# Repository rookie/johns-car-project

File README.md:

Overview
========

The goal of this project it to build a display for a car's instrument panel.

Display will include
- Engine coolant temp
- External temp
- Internal temp
- Speed (from GPS)
- Time (from GPS)
- Date (from GPS)
- Button input to toggle display between Metric to Imperial
- Button input to toggle time offset for Daylight Saving

Parts List
==========

- 1x Arduino Pro Mini 328 - https://www.sparkfun.com/products/11113
- 1x Adafruit 2.2" LCD - http://www.adafruit.com/products/1480
- 1x Adafruit Ultimate GPS - http://www.adafruit.com/products/746
- 3x ACDelco / GM Ambient Temperature Sensor (10K @ 25°C) - http://www.newgmparts.com/oe-gm/15936931

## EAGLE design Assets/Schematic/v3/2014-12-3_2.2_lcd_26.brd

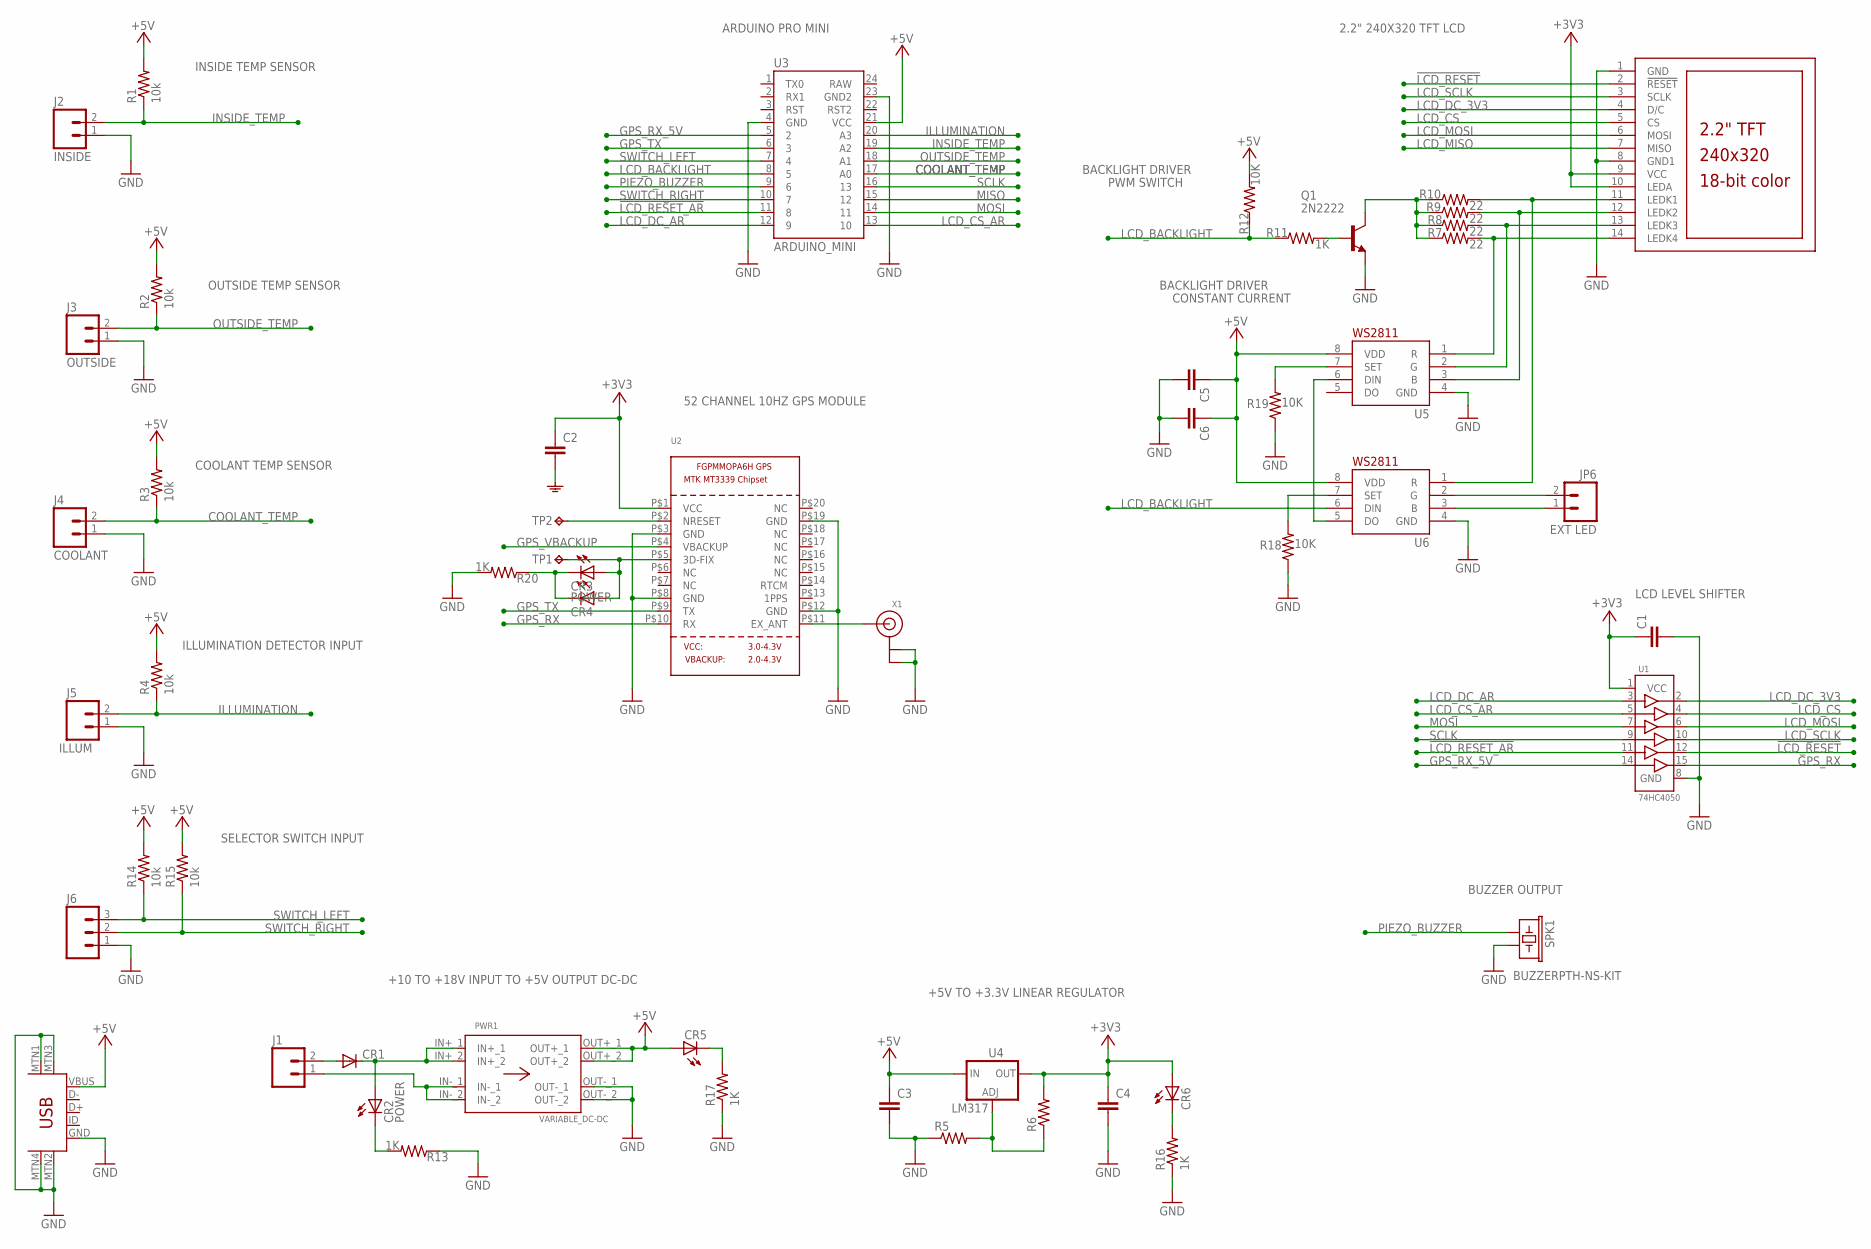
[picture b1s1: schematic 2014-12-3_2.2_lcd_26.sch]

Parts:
C1, C2, C3, C4, C5, C6: CAP0805; 0805
CR1: DIODESMB; SMB-DIODE
CR2, CR3: POWER; LED3MM
CR4, CR5, CR6: LED0603; LED-0603
J1: M02POLAR; MOLEX-1X2
J2: INSIDE; MOLEX-1X2
J3: OUTSIDE; MOLEX-1X2
J4: COOLANT; MOLEX-1X2
J5: ILLUM; MOLEX-1X2
J6: M03POLAR; MOLEX-1X3
JP6: EXT LED; MOLEX-1X2
PWR1: VARIABLE_DC-DC
Q1: 2N2222; TO92
R1, R2, R3, R4, R14, R15: 10k; 0805
R5, R6: RESISTOR0805-RES; 0805
R7, R8, R9, R10: 22; 0805
R11, R13, R16, R17, R20: 1K; 0805
R12, R18, R19: 10K; 0805
SPK1: BUZZERPTH-NS-KIT; BUZZER-12MM-NS-KIT
TP1, TP2: TPPAD1-13; P1-13
U1: 74HC4050; SO16
U2: GPS_FGPMMOPA6H; FGPMMOPA6H
U3: ARDUINO_MINI
U4: LM317; SOT223
U5, U6: WS2811-SOP8; SO08-SKINNYPADS
U$2: 2.2_LCD
USB: USB-MINIB-5PIN; USB-MINIB
X1: ANTENNA_U.FL; U.FL

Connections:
!LCD_RESET: U1.12, U$2.2 (!RESET)
!LCD_RESET_AR: U1.11, U3.11 (8)
+3V3: C1.1, C2.1, C4.1, CR6.A, R6.2, U1.1 (VCC), U2.P$1 (VCC), U4.2 (OUT), U$2.9 (VCC), U$2.10 (LEDA)
+5V: C3.1, C5.1, C6.1, CR5.A, PWR1.OUT+_1, PWR1.OUT+_2, R1.2, R2.2, R3.2, R4.2, R12.2, R14.2, R15.2, U3.21 (VCC), U4.3 (IN), U5.8 (VDD), U6.8 (VDD), USB.VBUS
COOLANT_TEMP: J4.2, R3.1, U3.17 (A0)
GND: C1.2, C3.2, C4.2, C5.2, C6.2, J2.1, J3.1, J4.1, J5.1, J6.1, PWR1.OUT-_1, PWR1.OUT-_2, Q1.1 (E), R5.1, R13.1, R16.1, R17.1, R18.1, R19.1, R20.2, SPK1.- (2), U1.8 (GND), U2.P$3 (GND), U2.P$8 (GND), U2.P$12 (GND), U2.P$19 (GND), U3.4 (GND), U3.23 (GND2), U5.4 (GND), U6.4 (GND), U$2.1 (GND), U$2.8 (GND1), USB.GND, USB.MTN1 (MTN2), USB.MTN2 (MTN3), USB.MTN3 (MTN1), USB.MTN4, X1.1 (GND), X1.2 (GND)
GPS_RX: U1.15, U2.P$10 (RX)
GPS_RX_5V: U1.14, U3.5 (2)
GPS_TX: U2.P$9 (TX), U3.6 (3)
GPS_VBACKUP: U2.P$4 (VBACKUP)
ILLUMINATION: J5.2, R4.1, U3.20 (A3)
INSIDE_TEMP: J2.2, R1.1, U3.19 (A2)
LCD_BACKLIGHT: R11.1, R12.1, U3.8 (5), U6.6 (DIN)
LCD_CS: U1.4, U$2.5 (CS)
LCD_CS_AR: U1.5, U3.13 (10)
LCD_DC_3V3: U1.2, U$2.4 (D/C)
LCD_DC_AR: U1.3, U3.12 (9)
LCD_MISO: U$2.7 (MISO)
LCD_MOSI: U1.6, U$2.6 (MOSI)
LCD_SCLK: U1.10, U$2.3 (SCLK)
MISO: U3.15 (12)
MOSI: U1.7, U3.14 (11)
unnamed: TP2.TP, U2.P$2 (NRESET)
unnamed: U2.P$11 (EX_ANT), X1.3 (SIGNAL)
unnamed: R7.2, U5.1 (R), U$2.14 (LEDK4)
unnamed: R8.2, U5.2 (G), U$2.13 (LEDK3)
unnamed: R9.2, U5.3 (B), U$2.12 (LEDK2)
unnamed: R5.2, R6.1, U4.1 (ADJ)
unnamed: R10.2, U6.1 (R), U$2.11 (LEDK1)
unnamed: Q1.3 (C), R7.1, R8.1, R9.1, R10.1
unnamed: Q1.2 (B), R11.2
unnamed: CR1.A, J1.2
unnamed: CR1.C, CR2.A, PWR1.IN+_1, PWR1.IN+_2
unnamed: J1.1, PWR1.IN-_1, PWR1.IN-_2
unnamed: JP6.2, U6.2 (G)
unnamed: CR3.K (C), CR4.C, R20.1
unnamed: CR2.K (C), R13.2
unnamed: CR3.A, CR4.A, TP1.TP, U2.P$5 (3D-FIX)
unnamed: CR6.C, R16.2
unnamed: CR5.C, R17.2
unnamed: U5.6 (DIN), U6.5 (DO)
unnamed: R18.2, U6.7 (SET)
unnamed: JP6.1, U6.3 (B)
unnamed: R19.2, U5.7 (SET)
OUTSIDE_TEMP: J3.2, R2.1, U3.18 (A1)
P$1: C2.2
PIEZO_BUZZER: SPK1.+ (1), U3.9 (6)
SCLK: U1.9, U3.16 (13)
SWITCH_LEFT: J6.3, R14.1, U3.7 (4)
SWITCH_RIGHT: J6.2, R15.1, U3.10 (7)

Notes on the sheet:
ARDUINO PRO MINI
2.2" 240X320 TFT LCD
BACKLIGHT DRIVER
CONSTANT CURRENT
PWM SWITCH
LCD LEVEL SHIFTER
BUZZER OUTPUT
+5V TO +3.3V LINEAR REGULATOR
+10 TO +18V INPUT TO +5V OUTPUT DC-DC
SELECTOR SWITCH INPUT
ILLUMINATION DETECTOR INPUT
COOLANT TEMP SENSOR
OUTSIDE TEMP SENSOR
INSIDE TEMP SENSOR
52 CHANNEL 10HZ GPS MODULE

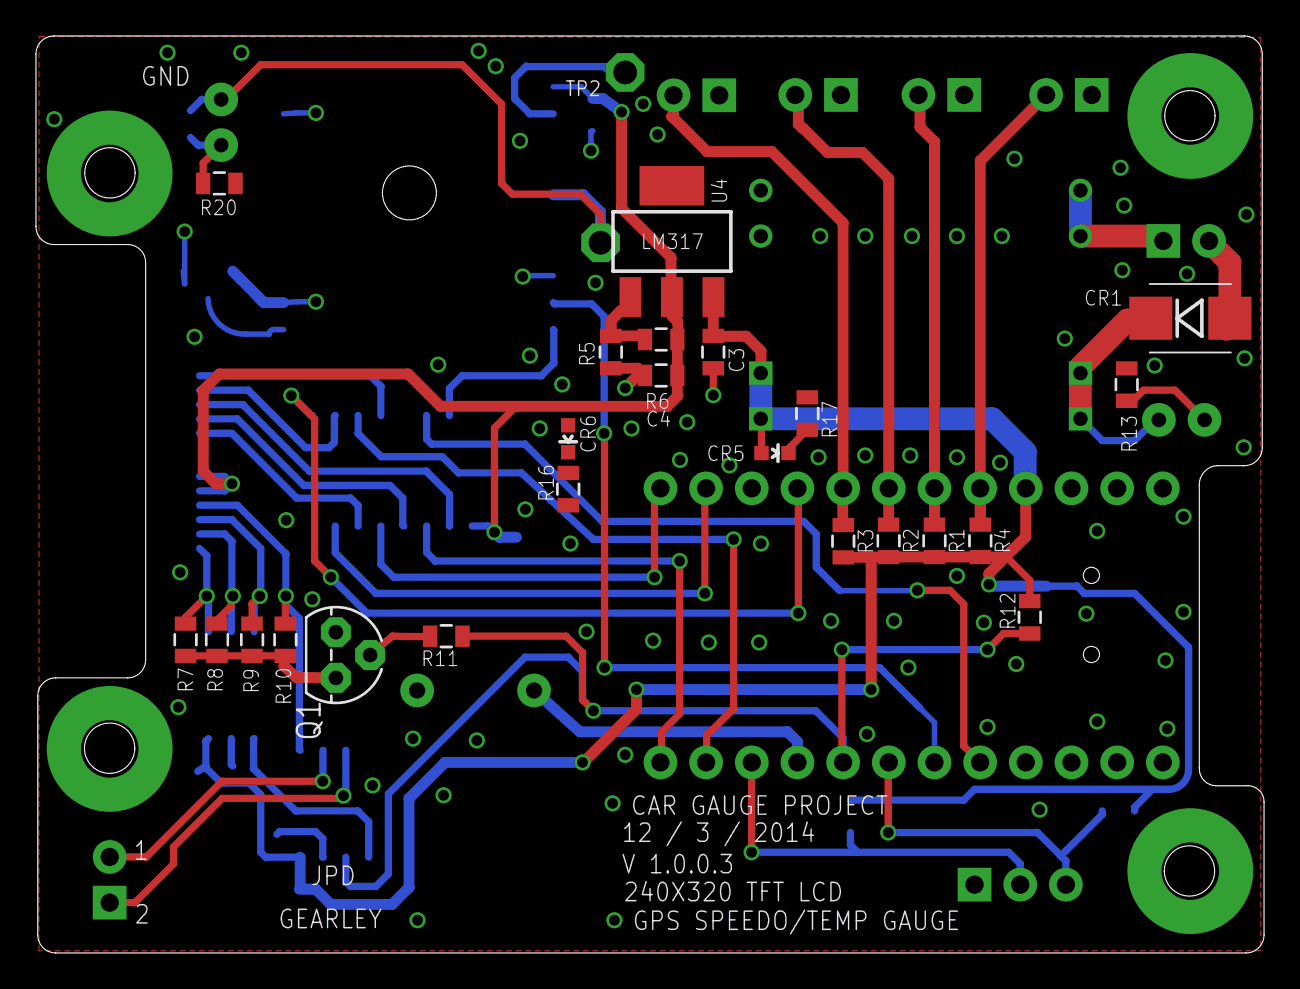
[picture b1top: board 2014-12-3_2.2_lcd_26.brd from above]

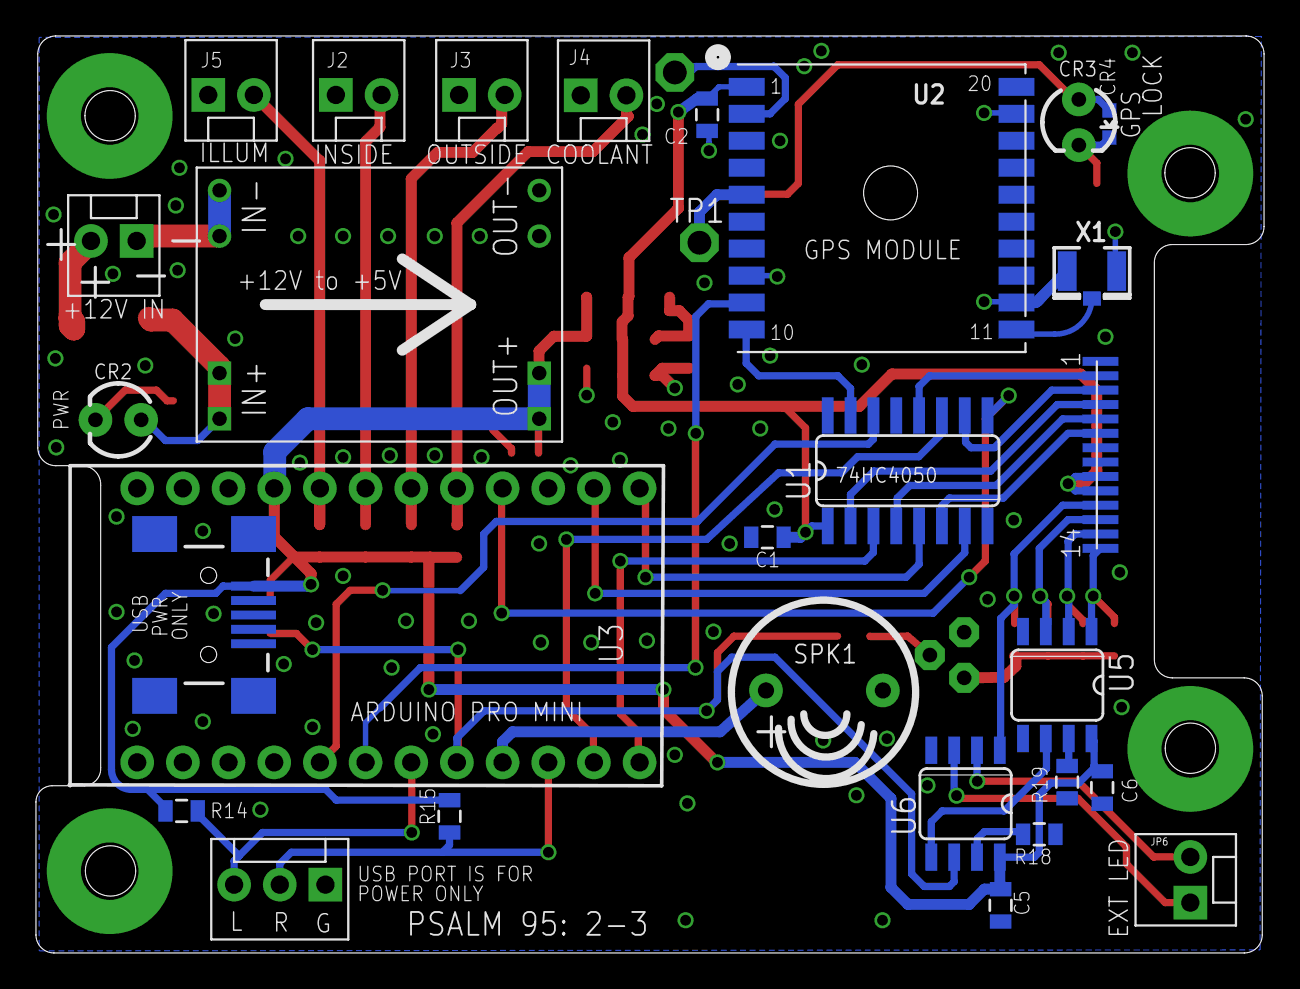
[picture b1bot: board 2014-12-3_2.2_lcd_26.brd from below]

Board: 2 copper layers, 68.3 x 51.0 mm, 53 parts (29 on the bottom side), 46 nets.

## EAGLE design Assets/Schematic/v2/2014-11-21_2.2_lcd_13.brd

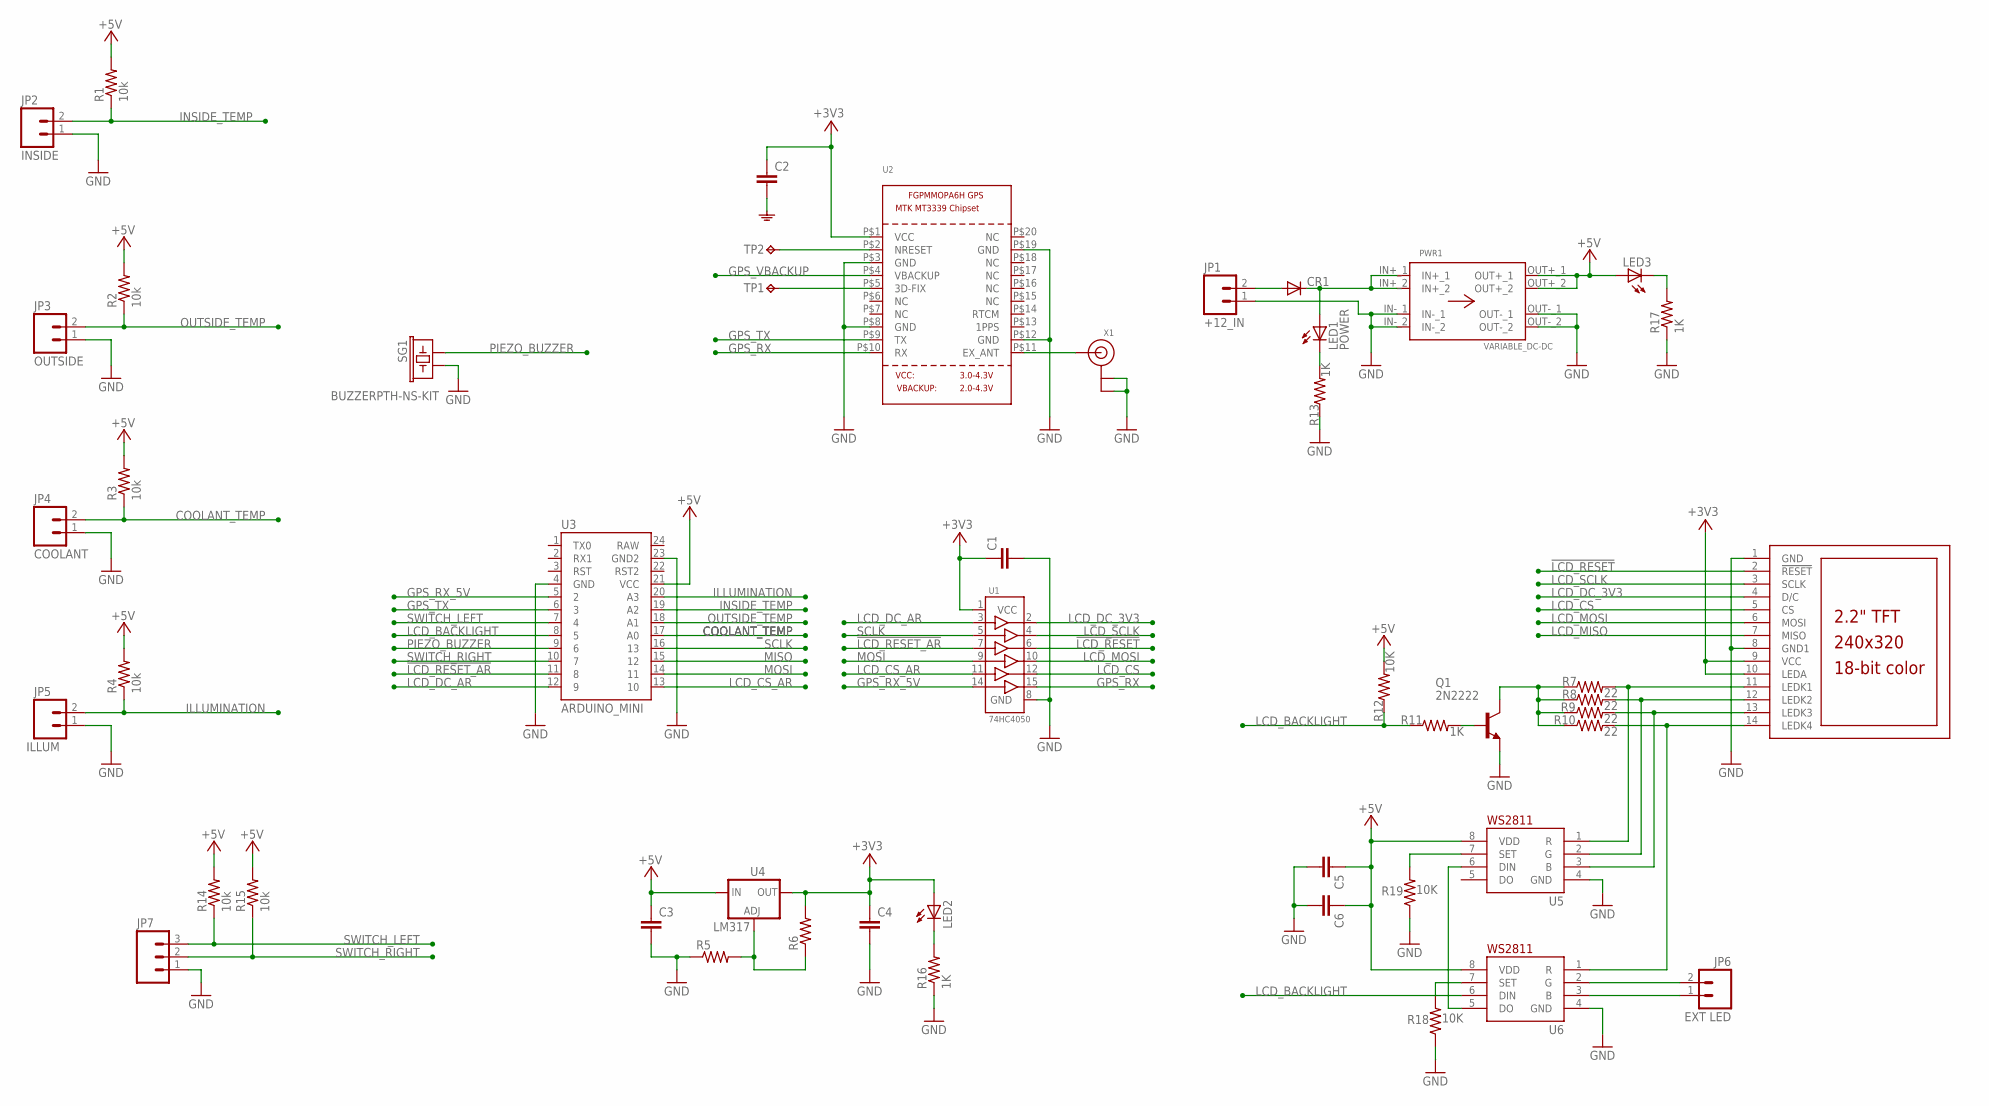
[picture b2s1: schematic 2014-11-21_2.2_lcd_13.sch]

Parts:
C1, C2, C3, C4: CAP0805; 0805
C5, C6: CAP0603-CAP; 0603-CAP
CR1: DIODESMA-ALT; SMA-DIODE_ALT
JP1: +12_IN; JST-2-PTH-VERT
JP2: INSIDE; JST-2-PTH-VERT
JP3: OUTSIDE; JST-2-PTH-VERT
JP4: COOLANT; JST-2-PTH-VERT
JP5: ILLUM; JST-2-PTH-VERT
JP6: EXT LED; JST-2-PTH-VERT
JP7: M03POLAR; MOLEX-1X3
LED1: POWER; LED3MM
LED2, LED3: LED0603; LED-0603
PWR1: VARIABLE_DC-DC
Q1: 2N2222; TO92
R1, R2, R3, R4, R14, R15: 10k; 0805
R5, R6: RESISTOR0805-RES; 0805
R7, R8, R9, R10: 22; 0805
R11, R13, R16, R17: 1K; 0805
R12, R18, R19: 10K; 0805
SG1: BUZZERPTH-NS-KIT; BUZZER-12MM-NS-KIT
TP1, TP2: TPPAD1-13; P1-13
U1: 74HC4050; SO16
U2: GPS_FGPMMOPA6H; FGPMMOPA6H
U3: ARDUINO_MINI
U4: LM317; SOT223
U5, U6: WS2811-SOP8; SO08-SKINNYPADS
U$1: 2.2_LCD
X1: ANTENNA_U.FL; U.FL

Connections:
!LCD_RESET: U1.6, U$1.2 (!RESET)
!LCD_RESET_AR: U1.7, U3.11 (8)
+3V3: C1.1, C2.1, C4.1, LED2.A, R6.2, U1.1 (VCC), U2.P$1 (VCC), U4.2 (OUT), U$1.9 (VCC), U$1.10 (LEDA)
+5V: C3.1, C5.1, C6.1, LED3.A, PWR1.OUT+_1, PWR1.OUT+_2, R1.2, R2.2, R3.2, R4.2, R12.2, R14.2, R15.2, U3.21 (VCC), U4.3 (IN), U5.8 (VDD), U6.8 (VDD)
COOLANT_TEMP: JP4.2, R3.1, U3.17 (A0)
GND: C1.2, C3.2, C4.2, C5.2, C6.2, JP1.1, JP2.1, JP3.1, JP4.1, JP5.1, JP7.1, PWR1.IN-_1, PWR1.IN-_2, PWR1.OUT-_1, PWR1.OUT-_2, Q1.1 (E), R5.1, R13.1, R16.1, R17.1, R18.1, R19.1, SG1.- (2), U1.8 (GND), U2.P$3 (GND), U2.P$8 (GND), U2.P$12 (GND), U2.P$19 (GND), U3.4 (GND), U3.23 (GND2), U5.4 (GND), U6.4 (GND), U$1.1 (GND), U$1.8 (GND1), X1.1 (GND), X1.2 (GND)
GPS_RX: U1.15, U2.P$10 (RX)
GPS_RX_5V: U1.14, U3.5 (2)
GPS_TX: U2.P$9 (TX), U3.6 (3)
GPS_VBACKUP: U2.P$4 (VBACKUP)
ILLUMINATION: JP5.2, R4.1, U3.20 (A3)
INSIDE_TEMP: JP2.2, R1.1, U3.19 (A2)
LCD_BACKLIGHT: R11.1, R12.1, U3.8 (5), U6.6 (DIN)
LCD_CS: U1.12, U$1.5 (CS)
LCD_CS_AR: U1.11, U3.13 (10)
LCD_DC_3V3: U1.2, U$1.4 (D/C)
LCD_DC_AR: U1.3, U3.12 (9)
LCD_MISO: U$1.7 (MISO)
LCD_MOSI: U1.10, U$1.6 (MOSI)
LCD_SCLK: U1.4, U$1.3 (SCLK)
MISO: U3.15 (12)
MOSI: U1.9, U3.14 (11)
unnamed: TP2.TP, U2.P$2 (NRESET)
unnamed: U2.P$11 (EX_ANT), X1.3 (SIGNAL)
unnamed: R7.2, U5.1 (R), U$1.11 (LEDK1)
unnamed: R8.2, U5.2 (G), U$1.12 (LEDK2)
unnamed: R9.2, U5.3 (B), U$1.13 (LEDK3)
unnamed: R5.2, R6.1, U4.1 (ADJ)
unnamed: R10.2, U6.1 (R), U$1.14 (LEDK4)
unnamed: Q1.3 (C), R7.1, R8.1, R9.1, R10.1
unnamed: Q1.2 (B), R11.2
unnamed: CR1.A, JP1.2
unnamed: CR1.C, LED1.A, PWR1.IN+_1, PWR1.IN+_2
unnamed: JP6.2, U6.2 (G)
unnamed: LED1.K (C), R13.2
unnamed: TP1.TP, U2.P$5 (3D-FIX)
unnamed: LED2.C, R16.2
unnamed: LED3.C, R17.2
unnamed: U5.6 (DIN), U6.5 (DO)
unnamed: R18.2, U6.7 (SET)
unnamed: JP6.1, U6.3 (B)
unnamed: R19.2, U5.7 (SET)
OUTSIDE_TEMP: JP3.2, R2.1, U3.18 (A1)
P$1: C2.2
PIEZO_BUZZER: SG1.+ (1), U3.9 (6)
SCLK: U1.5, U3.16 (13)
SWITCH_LEFT: JP7.3, R14.1, U3.7 (4)
SWITCH_RIGHT: JP7.2, R15.1, U3.10 (7)

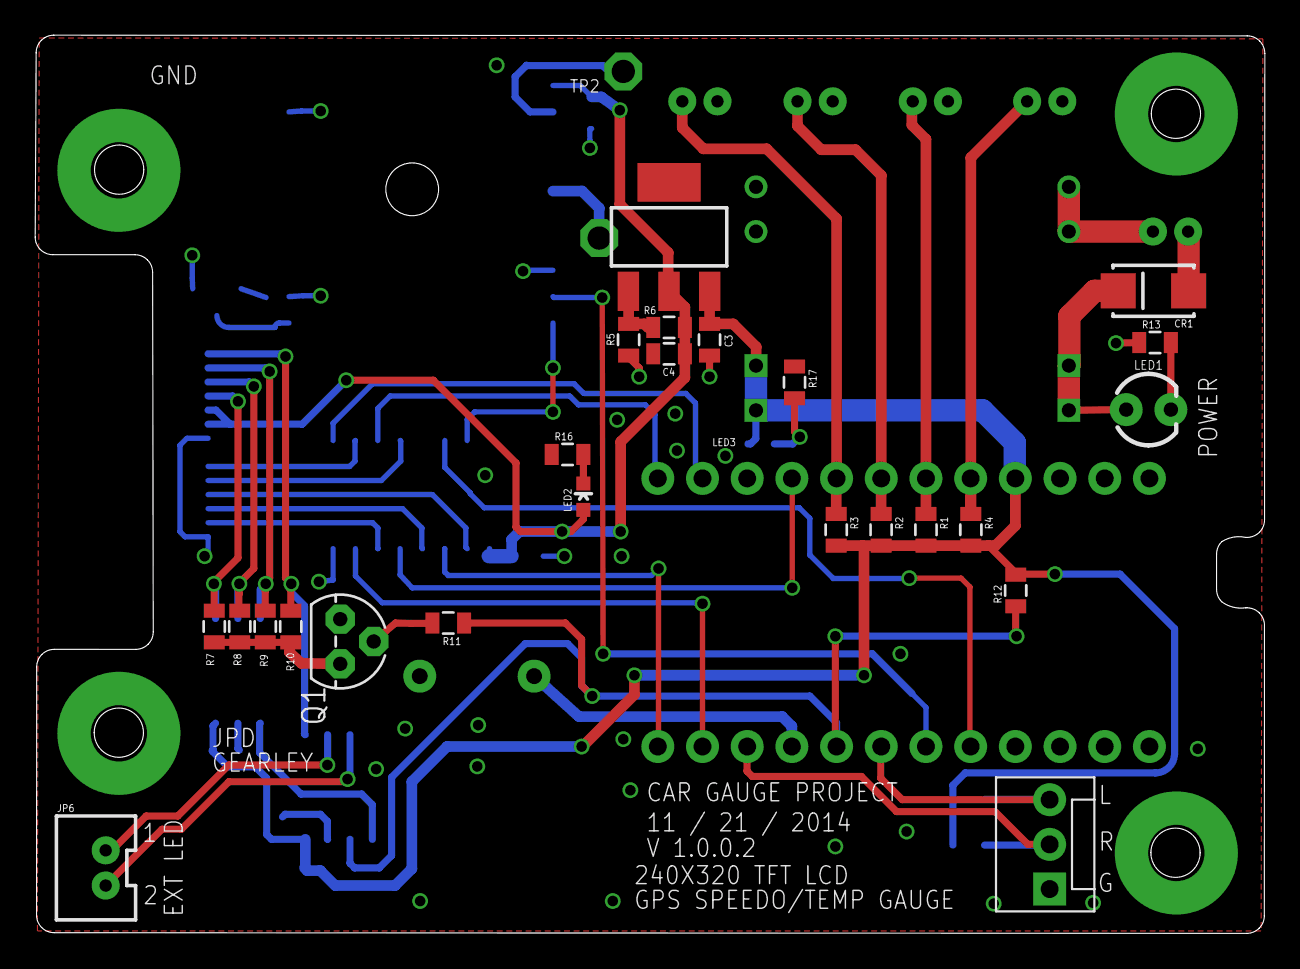
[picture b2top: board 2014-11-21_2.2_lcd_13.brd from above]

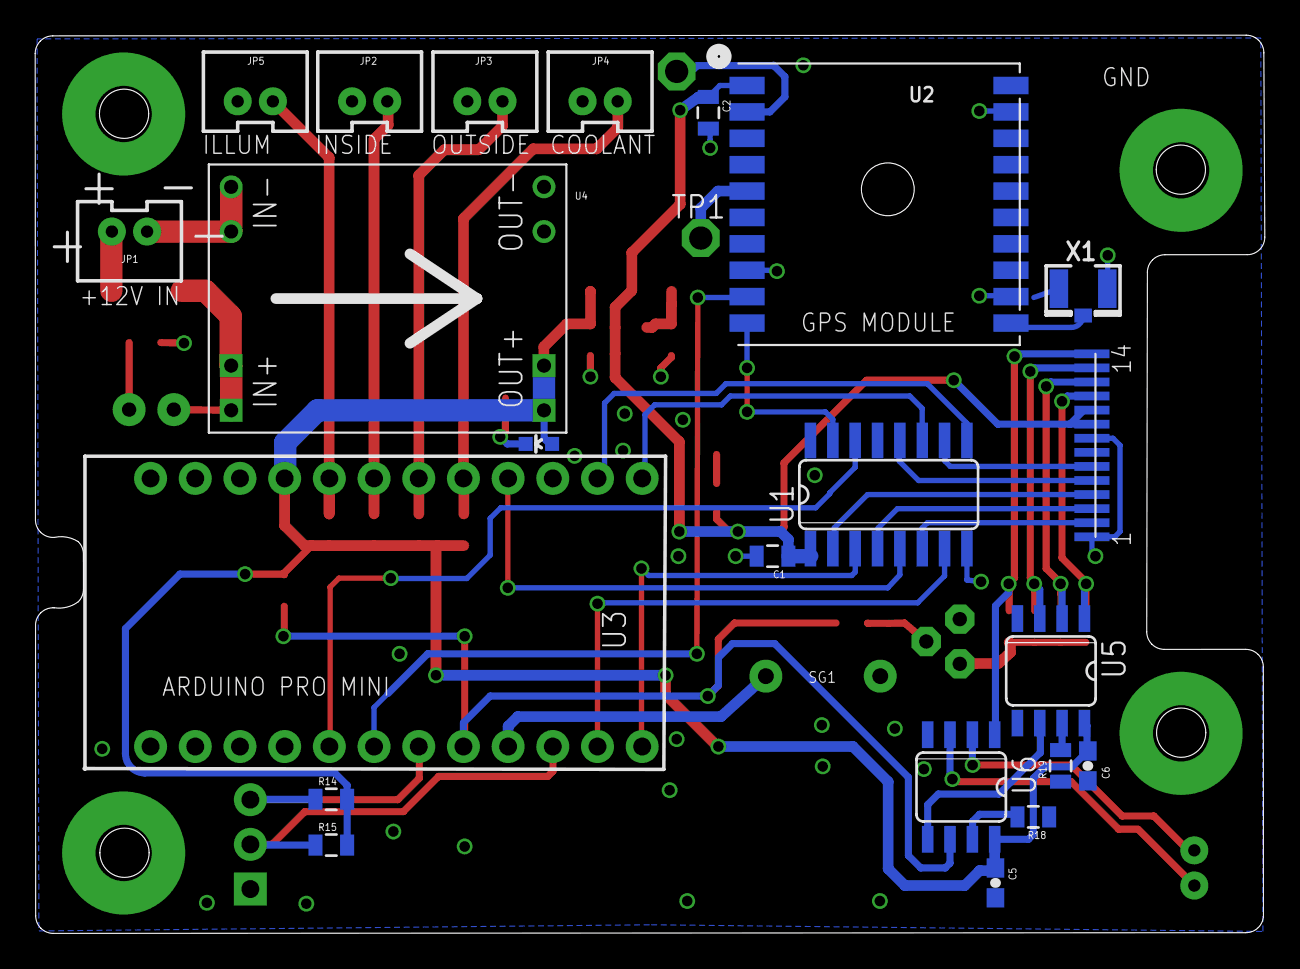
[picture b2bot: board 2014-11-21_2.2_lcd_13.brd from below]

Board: 2 copper layers, 69.9 x 51.0 mm, 49 parts (24 on the bottom side), 44 nets.

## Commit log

2014-04-17 initial commit from example
2014-04-18 add some tests and some folders
2014-04-18 fix duplicate tempTest
2014-04-18 add lcd printing of analog data
2014-04-18 added colorPickerLCD sketch for testing colors
2014-04-18 add initial gauge design from john
2014-04-18 Add read me
2014-04-18 Add background color to the changing text.
2014-04-18 Rotate screen 90º
2014-04-18 Add basic boxes for Johns initial UI
2014-04-18 Fill in half of the temp boxes
2014-04-18 Add gps library and initial structs for global storage
2014-04-18 Add string processing for output
    - convert numbers to strings for C and F
    - only update the strings and the screen when numbers are changed
    - turn off interrupts for now
2014-04-18 Update UI drawing
    - Add text to the initial UI (too long)
    - Test º degrees symbol text support
    - Test drawBitmap function
    - Fix some ui location issues
2014-04-19 Add a processing.pde file for UI Mock ups and testing
2014-04-19 Update drawing of 8 and 9
    - Add 8 and 9 drawing to pde sample UI
    - Add 8 and 9 drawing to ino LCD drawing
2014-04-19 Update rotation
    it seems like that should not have worked...
2014-04-19 Fix rotation bug
    - Rotation is now set to 1 (90º)
    - Revert changes to drawBitmap because Johns library doesn't have the changes yet.
2014-04-19 Fix colorPicker analog mapping
    - color565 function wanted 0-255 as values
2014-04-19 Turn on interrupt for GPS data
2014-04-19 Updated to include speed
    - Should be ready to take the gps/lcd out on the road to test
    - Only refreshed speed when it changes
    - Updated the refresh speed to 500ms
2014-04-19 Prepare for large speed type
    - Add rest of the 0-9 numbers
    - Print the numbers (commented out for now)
    - John needs my version of the Adafruit-GFX library before he can test it
2014-04-30 Add speed number drawing
    - Add new functions for draw bitmap with background
    - Draw large speedometer numbers
2014-05-02 Fix bug where speed wasn't working
    - Fix speed bug (wasn't casting to an int)
    - Add rest of the numbers other than 8,9
    - Add blank drawing for zeroing out 10s place when going from 10->9
    - Fix zero bitmap error
    - Add lcd backlight turn on in all lcd sketches (pin 5 high)
    - Add initial schematic from John (pdf)
2014-05-02 Speed up updates
    - Set to 5hz update speed
    - Updates every 500 ms
    - Remove adafruit logo
    - Remove º symbol
    - Remove Serial prints in gps updates
2014-05-05 Fix bitmaps for numbers 5 and 4
2014-05-05 Reorganize and optimize
    - Move calculate and updateUI to main loop
    - Change around how speed is calculated and updated
    - Remove antenna output
2014-05-05 Add some tests and receive less gps info
    - Add Tests for speed display, they are commented out in the main loop
    - Get less data from GPS
2014-05-05 Add bar UI test functions
    - Uncomment `testUIBars();` from the main `loop()` to watch the tests
    - Draft
2014-05-06 Small updates to UI temp bar tests
2014-05-06 Add test functions for temps
    - Add sweep for temps
    - Add ui bars for coolant and outside temp
2014-05-06 Add coolant Icon
    - move processing projects under processing directory
2014-05-06 Add processing sketch to create icons
    - Left click to add pixels, right click to remove
    - You can change `gridWidth` and `gridHeight` but for now keep `gridWidth` as a multiple of eight
    - Send me the binary output if you want me to use the icon for something
2014-05-06 Separate array updates
    - Add header to image updates so the arrays don't blend together
2014-05-08 Add Johns temperature calculation for inside temp sensor
    - From John: TemperatureF = (((90000 - (100 * A/D)) / 619)
    - That is ºF with the GM sensor in a 5v system with a 15k pull up.
2014-05-09 Add calculation for coolant sensor
    - Fix some issues with unsigned ints
    - Added calculated temp to the displayF/C struct
2014-05-09 Add Inside bar update
    - Add drawUIInsideTemp() function, add to updateUI()
    - Update drawUIRightBar() function for new drawing
    - Fix testUITemp() function, must comment out calculateUI() to run
2014-05-09 Updated Coolant temp calculation from John
    - New calculation: DegF = 69529 - 9334 * ln(analogValue) /100
2014-05-09 Update bitmap assets
    - Add Johns new gauge2
    - Add Johns new thermometer bitmap
    - Add thermometer bitmap to gridDraw to array
    - Add thermometer bitmap to project
2014-05-30 Add new assets
    - New gauge look
    - Font for other text
    - New font for speed
2014-05-30 Add font assets
    - Create bmp parser and generate easily cleaned up c code
2014-08-05 Initial assets for larger screen
    - Updated gauge design
    - New speed font
    - New symbols
2014-08-05 Updated bmpConverter
    - Add support for any bmp image
    - Add byte padding of output
2014-08-29 Started work on large screen convert
    - Add time library
    - Commit before il 2.2 screen test
2014-08-29 Update for larger screen
    - Update speedo drawing to draw quicker
2014-08-29 Add/delete segments based on last number displayed
    - Clip speed display at 99
    - Add/delete segments based on last number displayed
2014-08-29 Update for staging UI
    - Added bounding boxes for UI update
    - Updated some code in preparation for arduino 1.5, should work with 1.1
2014-09-04 Update with ui drawing
    - Added debug ui for positioning elements
    - Added rest of the ui
    - Added most of the time/date text
2014-09-05 Get coolant bar working
    - Only draw/delete enough of the coolant bar as changes
    - Add colon for time display
    - Add snowflake display
    - Still need to decide what to do with temp when only partially overlapping text
2014-09-05 Fix coolant bar text
    - Move coolant bar text to the right side when under 165
    - Change temp text to blue when negative (until dash symbol from John)
    - Move Coolant text down two pixels from 5 to 7
2014-09-10 Add demo mode
    - Add #define for DEMO_MODE
    - Fix issue #7 Coolant symbol draws white on white bar
2014-09-26 Update segments on Speed Font
    - Add more segments to speed font to fix the display issues
    - Remove some old unused functions for old seven segment drawing
2014-09-26 Add negative character for the small font
    - Add negative character
    - Remove blue color for negative numbers
    - Demo mode starts temps at negative
2014-09-26 Add C and KPH for metric display mode
    - Add C to small font
    - Add KPH to symbols
2014-09-26 Add dashes to speed font
    - Remove dashes from speed font
2014-09-26 Font tweaks
    - Add/remove flag on the 1,4 character for the speed font
2014-09-26 Redo segments to tweak font style
    - Add extra segment
    - Tweak size of segments to stylize speed font
    - Add speed font locations and sizes
2014-11-15 Update to use PDQ GFX library
    - Change includes
    - Change declaration of tft
    - Add extra lines to setup for library to not horribly fail
2014-12-06 Fix Daylight saving offset
    - Added one line for PDT and one for PST
    - Will add manual configuration later
2014-12-06 Add Metric / Imperial display modes
    - Add Celsius calculation
    - Add display checks for mode
2014-12-06 Smooth out temperature changes
    - Only update temp if analog value has changed by at least 2
2014-12-06 Add schematics for the boards
    - v2 is the current red board
    - v3 is at the board house and already bypassed, fixed display rotation
    - v4 has fixes from v2 and v3
2015-02-06 Convert to hardware serial
    - Use hardware serial to talk to GPS
    - Comment out debug lines
2015-02-06 Add debug flags
    - flag for demo mode
    - flag for fast updates
    - flag for fast baud
    - flag for show gps fix
2015-02-06 Add buttons and save to eeprom
    - left button for toggle dst. 0/+1
    - right button for toggle mph. imperial/metric
    - hide low speedo values
2015-02-06 Add some GPS parsing debug
    - Break up gps parsing input multiple lines to better debug when needed
2015-02-20 Debug and testing updated
    - Remove box around top temp bar
    - Add function drawJohnsBar() for potential new temp bar
    - Force into Imperial for demo mode
2015-03-24 Add new gauge picture
    - Add new gauge pictures for readme

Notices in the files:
parts and their libraries:
SparkFun-Boards: Licensing: CC v3.0 Share-Alike You are welcome to use this library for commercial purposes.
SparkFun-Connectors: Licensing: Creative Commons ShareAlike 4.0 International - https://creativecommons.org/licenses/by-sa/4.0
